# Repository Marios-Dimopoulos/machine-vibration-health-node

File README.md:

# machine-vibration-health-node

A secure edge vibration monitor for predictive maintenance, built on the STM32MP215F-DK.

The Cortex-M33 (Zephyr) samples an ADXL345 accelerometer and computes an FFT of the vibration.
The Cortex-A35 (Linux) receives the spectrum over RPMsg, detects anomalies and publishes alerts
over MQTT/TLS. Underneath: secure boot, A/B updates with RAUC, a read-only dm-verity rootfs,
a custom KiCad HAT, and a hardware-in-the-loop test rig.

This is an educational portfolio project, a work in progress.

- [Project plan](docs/plan.md): phases and the proof that ends each one
- [Architecture](docs/architecture.md): the current state of the system
- [Decisions](docs/decisions/): ADRs

## Building the Linux image

How I build `vibration-image` for the A35, with Yocto (scarthgap) and ST's OpenSTLinux layers.

### Build host

- Ubuntu 24.04 in WSL2, with the project in the Linux filesystem (`~/...`), never under `/mnt/c`:
  Yocto needs a case-sensitive, fast filesystem.
- The host packages listed in the Yocto Project 5.0 manual ("Required Packages for the Build Host").
- `chrony` instead of `systemd-timesyncd`: WSL's clock drifted and jumped backwards under load
  ("Clock skew detected" in meson, probably also the cause of a failed OpenSSL build). chrony
  corrects it by slewing instead of jumping.

### 1. Get the layers

The layers are those of ST's manifest `openstlinux-6.6-yocto-scarthgap-mpu-v26.06.10`
(github.com/STMicroelectronics/oe-manifest), cloned by hand at its pinned commits. They live in
`yocto/layers/`, which git ignores, next to my layer `meta-vibration-node` (in this repository).

| Repository | Directory in `yocto/layers/` | Commit |
|---|---|---|
| https://git.openembedded.org/openembedded-core | `openembedded-core` | `52380df998b3a8fe6a091f8547434a3231320a8e` (yocto-5.0.17) |
| https://git.openembedded.org/bitbake | `openembedded-core/bitbake` | `b2404004135b669f8258c85c7b5aed4570a805c7` |
| https://git.openembedded.org/meta-openembedded | `meta-openembedded` | `5124ac4a658899158f4a7a2ddf1d2ca931ec7d0e` |
| https://github.com/STMicroelectronics/meta-st-stm32mp | `meta-st/meta-st-stm32mp` | `49046b2a0ad4dc29117025c94838b9befff86f23` |
| https://github.com/STMicroelectronics/meta-st-openstlinux | `meta-st/meta-st-openstlinux` | `b0316f706bcf34e8449d43aba3c630030f2cc366` |
| https://github.com/STMicroelectronics/meta-st-stm32mp-addons | `meta-st/meta-st-stm32mp-addons` | `ad667afe266eb1ca706bf92ea6d99cc9ec74d662` |
| https://github.com/STMicroelectronics/meta-st-scripts | `meta-st/scripts` | `8826802b453ef2ead61b07c7bc5ab525a405df04` |

For each one, from `yocto/`:

```
git clone <repository> layers/<directory>
git -C layers/<directory> checkout <commit>
```

Clone `openembedded-core` before `bitbake`, since bitbake goes inside it.

### 2. Create the build directory

From `yocto/`, with ST's configuration templates:

```
TEMPLATECONF=$PWD/layers/meta-st/meta-st-openstlinux/conf/templates/default \
    source layers/openembedded-core/oe-init-build-env build-openstlinuxweston-stm32mp21-disco
```

This creates `conf/local.conf` and `conf/bblayers.conf` and moves into the build directory. In a new
shell later, the same `source` line (without `TEMPLATECONF`) sets up the environment again.

The downloads and the shared state cache go to `yocto/oe-downloads/` and `yocto/oe-sstate-cache/`
(ST's template), outside the build directory, so other build directories can reuse them.

### 3. Configure `conf/local.conf`

`local.conf` is not in git: it holds the settings of this build directory on this PC. My changes to
ST's template:

```
MACHINE = "stm32mp21-disco"
DISTRO = "openstlinux-weston"
ACCEPT_EULA_stm32mp21-disco = "1"
BB_NUMBER_THREADS = "6"
PARALLEL_MAKE = "-j 6"
PARALLEL_MAKEINST:pn-openssl = "-j 1"
PARALLEL_MAKEINST:pn-openssl-native = "-j 1"
BUILDHISTORY_COMMIT = "0"
```

and the template's `INHERIT += "rm_work"` commented out.

- `ACCEPT_EULA_...`: accepts ST's license (SLA0048) for the firmware parts of the BSP.
- `BB_NUMBER_THREADS`, `PARALLEL_MAKE`: 6 of my 8 cores, which leaves the PC usable and needs less RAM.
- `PARALLEL_MAKEINST` for OpenSSL: its `make install` rebuilt the libraries in parallel and failed
  with undefined references.
- `BUILDHISTORY_COMMIT = "0"`: the template already enables buildhistory, which records the packages
  of each image and who pulled them in (`buildhistory/images/.../depends.dot`). With `0` it only
  writes the files and does not make a git commit at every build.
- `rm_work` off: it deleted bison-native's work directory, which bison's built-in m4 path points into,
  and glibc then failed with "m4 subprocess failed".

### 4. Add the layers

From the build directory:

```
bitbake-layers add-layer ../layers/meta-openembedded/meta-oe
bitbake-layers add-layer ../layers/meta-openembedded/meta-python
bitbake-layers add-layer ../layers/meta-vibration-node
```

ST's template already lists openembedded-core, the other meta-openembedded layers and ST's layers.

### 5. Build

```
bitbake vibration-image
```

The first build compiles everything (several hours); later builds reuse the shared state cache.

### 6. Create the SD card image

In the deploy directory, `tmp-glibc/deploy/images/stm32mp21-disco/`:

```
SDCARD_SIZE=768 ./scripts/create_sdcard_from_flashlayout.sh \
    flashlayout_vibration-image/optee/FlashLayout_sdcard_stm32mp215f-dk-optee.tsv
```

This writes `FlashLayout_sdcard_stm32mp215f-dk-optee.raw` (768 MB) next to the script.
`SDCARD_SIZE` sets the size of the `.raw`; without it, ST's script makes it 4915 MB. Every image
writes a `.raw` with this same name, so check its time before using it.

### 7. Write and boot

Write the `.raw` to a microSD card (I use Raspberry Pi Imager on Windows, "Use custom"). Check the
target disk twice: writing to the wrong disk destroys its data.

Boot switches for microSD boot: BOOT0 ON, BOOT1-3 OFF (UM3571 Rev 1, p. 13). The A35 console is on
CN2 at 115200 baud. The board logs in as root automatically on the console (a development setting)
and is reachable over SSH on Ethernet (by its IP address; its hostname is `vibration-node`).

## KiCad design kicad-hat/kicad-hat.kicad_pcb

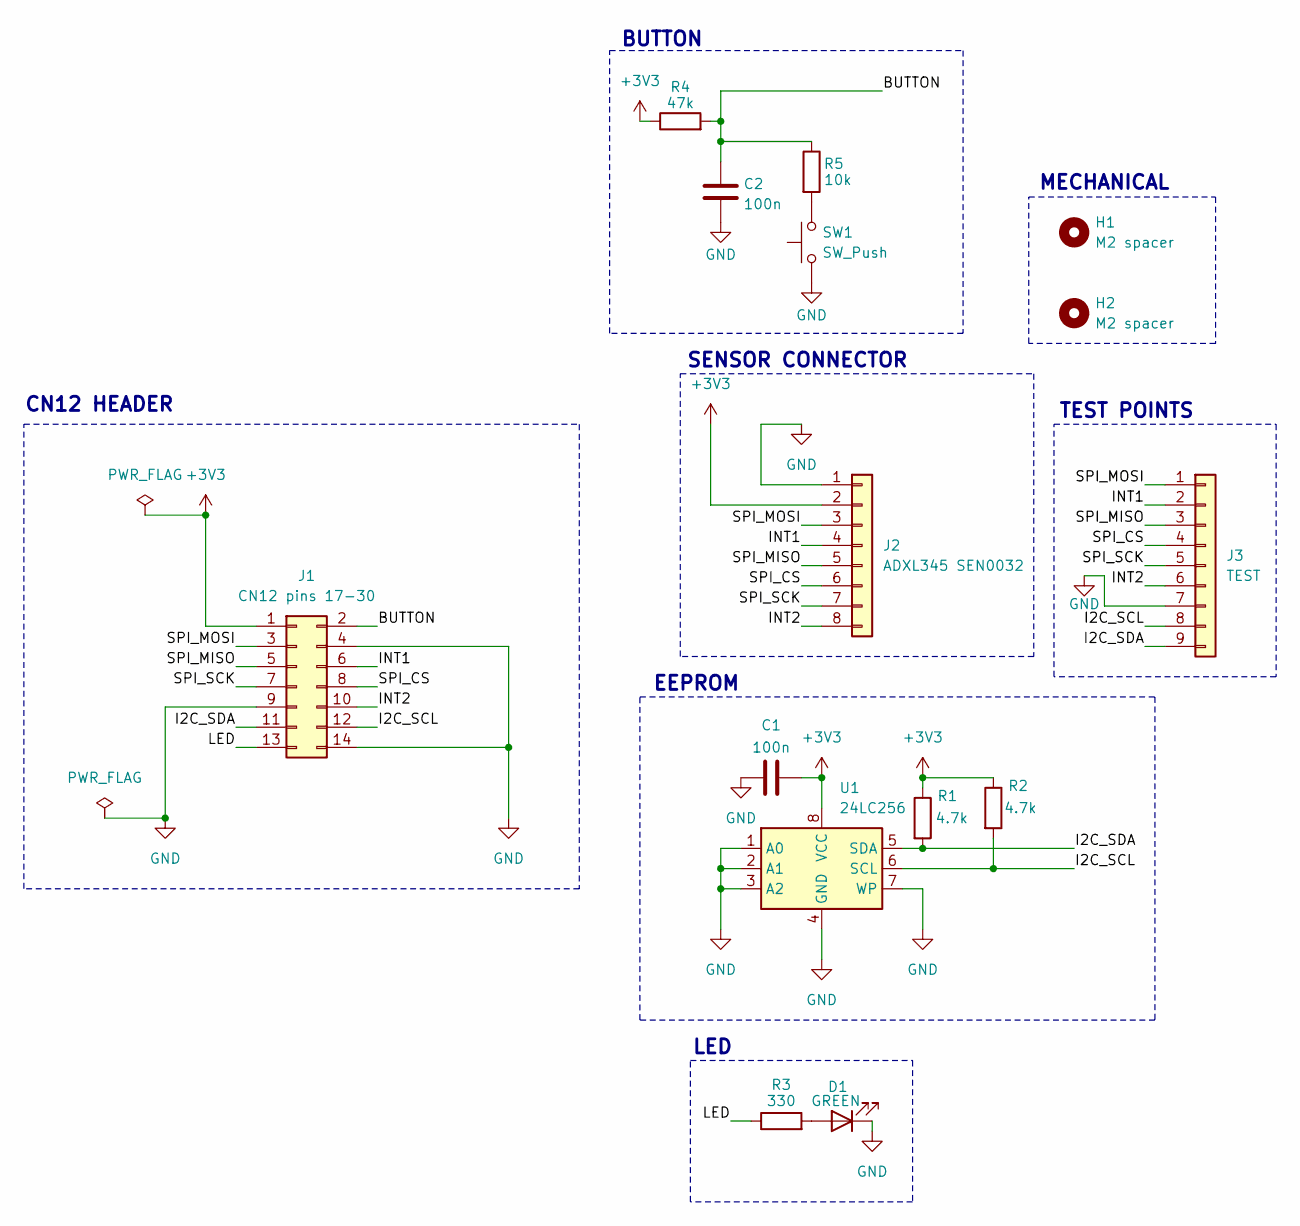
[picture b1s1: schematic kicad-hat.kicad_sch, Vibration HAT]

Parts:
C1, C2: 100n; C_Disc_D5.0mm_W2.5mm_P5.00mm
D1: GREEN; LED_D5.0mm
H1, H2: M2 spacer; MountingHole_2.2mm_M2
J1: CN12 pins 17-30; PinSocket_2x07_P2.54mm_Vertical
J2: ADXL345 SEN0032; PinSocket_1x08_P2.54mm_Vertical
J3: TEST; PinHeader_1x09_P2.54mm_Vertical
R1, R2: 4.7k; R_Axial_DIN0207_L6.3mm_D2.5mm_P7.62mm_Horizontal
R3: 330; R_Axial_DIN0207_L6.3mm_D2.5mm_P7.62mm_Horizontal
R4: 47k; R_Axial_DIN0207_L6.3mm_D2.5mm_P7.62mm_Horizontal
R5: 10k; R_Axial_DIN0207_L6.3mm_D2.5mm_P7.62mm_Horizontal
SW1: SW_Push; SW_Push_2pin_P5.08mm
U1: 24LC256; DIP-8_W7.62mm_Socket

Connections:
+3V3: C1.2, J1.1, J2.2, R1.1, R2.1, R4.1, U1.8 (VCC)
/BUTTON: C2.1, J1.2, R4.2, R5.1
/I2C_SCL: J1.12, J3.8, R2.2, U1.6 (SCL)
/I2C_SDA: J1.11, J3.9, R1.2, U1.5 (SDA)
/INT1: J1.6, J2.4, J3.2
/INT2: J1.10, J2.8, J3.6
/LED: J1.13, R3.1
/SPI_CS: J1.8, J2.6, J3.4
/SPI_MISO: J1.5, J2.5, J3.3
/SPI_MOSI: J1.3, J2.3, J3.1
/SPI_SCK: J1.7, J2.7, J3.5
GND: C1.1, C2.2, D1.1 (K), J1.4, J1.9, J1.14, J2.1, J3.7, SW1.1, U1.1 (A0), U1.2 (A1), U1.3 (A2), U1.4 (GND), U1.7 (WP)
unnamed: D1.2 (A), R3.2
unnamed: R5.2, SW1.2

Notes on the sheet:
SENSOR CONNECTOR
LED
BUTTON
EEPROM
CN12 HEADER
MECHANICAL
TEST POINTS

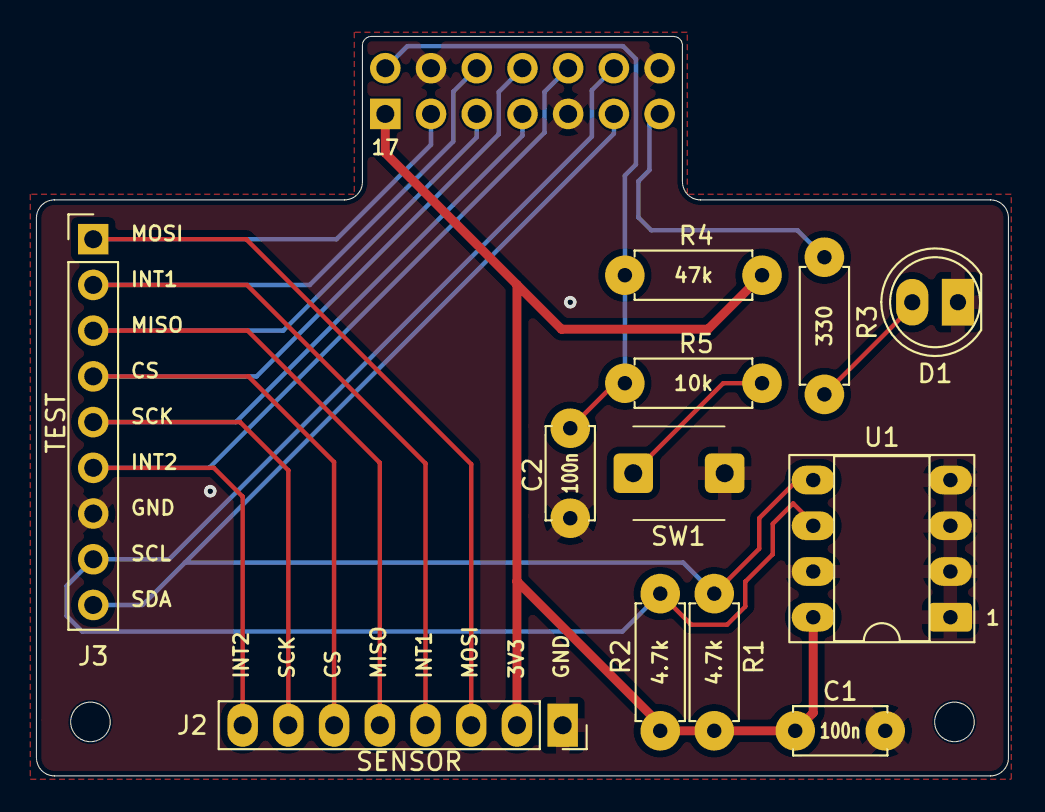
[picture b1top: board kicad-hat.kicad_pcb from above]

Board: 2 copper layers, 54.0 x 41.1 mm, 15 parts (1 on the bottom side), 14 nets.
